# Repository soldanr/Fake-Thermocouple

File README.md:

Fake-Thermocouple
=================
A DIY Thermocouple Test Circuit !
The circuit is a voltage divider  with a 150Kohm resistor and a 1Kohm precision potentiomenter (trim pot) powered by a 9 Volt Battery. To add a little character to the board we added some capacitors, an On-Off switch, an LED, a 5V voltage regulator  and the famous LM 324 Op-Amp acting like a Buffer Amplifier.

http://iddevlabs.blogspot.com/2014/09/diy-thermocouple-testing-circuit.html

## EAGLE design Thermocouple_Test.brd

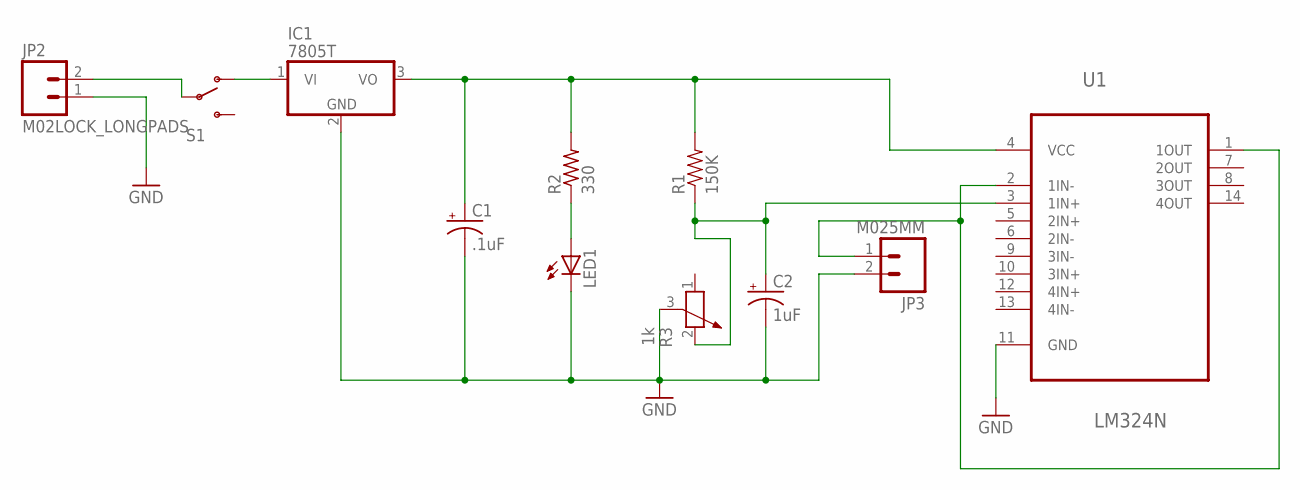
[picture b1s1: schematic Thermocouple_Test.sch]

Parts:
C1: .1uF; CPOL-RADIAL-10UF-25V-KIT
C2: 1uF; CPOL-RADIAL-10UF-25V-KIT
IC1: 7805T; TO220H
JP2: M02LOCK_LONGPADS; 1X02_LOCK_LONGPADS
JP3: M025MM; SCREWTERMINAL-5MM-2
LED1: LED_ELD260; LED_LD260
R1: 150K; AXIAL-0.5
R2: 330; 0204/7
R3: 1k; PT-SPIN
S1: SWITCH-SPDTPTH; SWITCH-SPDT
U1: LM324N; DIP254P762X508-14

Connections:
GND: C1.2 (-), C2.2 (-), IC1.2 (GND), JP2.1, JP3.2, LED1.K (C), R3.3, U1.11 (GND)
unnamed: C1.1 (+), IC1.3 (VO), R1.P$2 (2), R2.2, U1.4 (VCC)
unnamed: C2.1 (+), R1.P$1 (1), R3.2, U1.3 (1IN+)
unnamed: JP3.1, U1.1 (1OUT), U1.2 (1IN-)
unnamed: LED1.A, R2.1
unnamed: IC1.1 (VI), S1.1 (O)
unnamed: JP2.2, S1.2

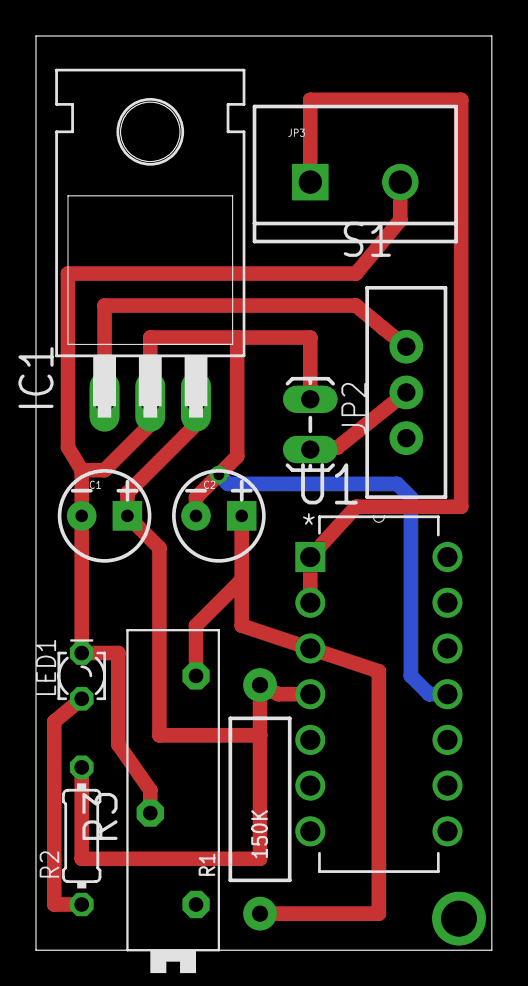
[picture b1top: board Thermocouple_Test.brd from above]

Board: 2 copper layers, 25.3 x 50.8 mm, 11 parts (0 on the bottom side), 7 nets.

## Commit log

2014-09-19 Files

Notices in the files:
parts and their libraries:
SparkFun-Capacitors: Licensing: Creative Commons ShareAlike 4.0 International - https://creativecommons.org/licenses/by-sa/4.0
